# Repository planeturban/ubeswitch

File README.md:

## 301
Needed to keep it clean. BOM and other stuff is over here -> https://github.com/planeturban/ubeswitchmk6

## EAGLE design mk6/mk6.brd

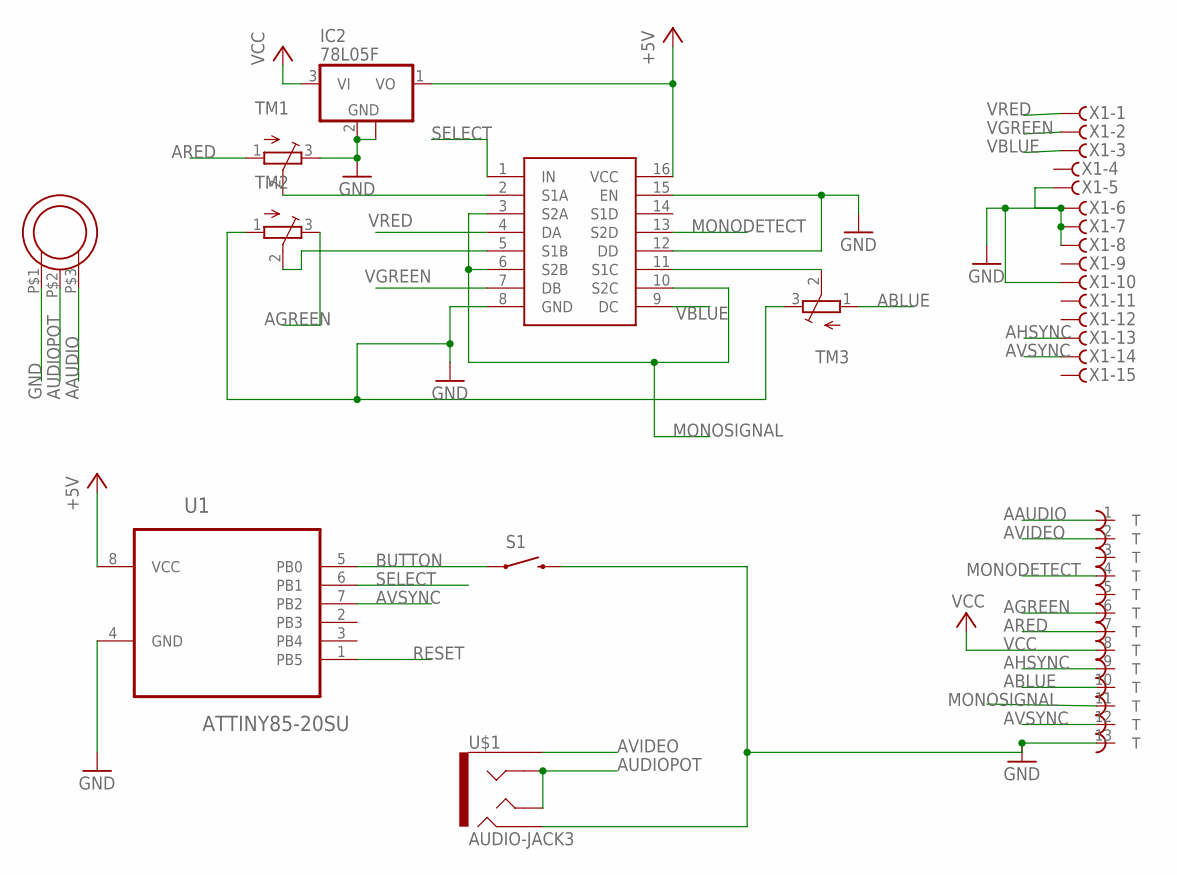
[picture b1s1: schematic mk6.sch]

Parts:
ATARIOUT: DIN13T; ADADS
IC2: 78L05F; SOT89
S1: SWITCH-MOMENTARY-2TACTILE-SWITCH-SMD-RIGHT-ANGLE; TACTILE_SWITCH-SMD-RIGHT-ANGLE
TM1, TM2, TM3: TRIMPOTTC33X; TC33X
TS5V330: V330; SOIC16N
U1: ATTINY85-20SU; SOIC127P798X216-8N
U$1: AUDIO-JACK3; AUDIO-JACK-TRRS-SMD
U$2: DB-1001N; THUMB_POT
X1: F15HDVS; HDF15V

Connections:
+5V: IC2.1 (VO), TS5V330.16 (VCC), U1.8 (VCC)
AAUDIO: ATARIOUT.1, U$2.P$3 (3)
ABLUE: ATARIOUT.10, TM3.1 (A)
AGREEN: ATARIOUT.6, TM2.3 (E)
AHSYNC: ATARIOUT.9, X1.13
ARED: ATARIOUT.7, TM1.1 (A)
AUDIOPOT: U$1.RING1, U$1.TIP, U$2.P$2 (2)
AVIDEO: ATARIOUT.2, U$1.EARTH
AVSYNC: ATARIOUT.12, U1.7 (PB2), X1.14
BUTTON: S1.1, U1.5 (PB0)
GND: ATARIOUT.13, IC2.2 (GND), IC2.2@1 (GND), S1.2, TM1.3 (E), TM2.1 (A), TM3.3 (E), TS5V330.8 (GND), TS5V330.12 (DD), TS5V330.15 (EN), U1.4 (GND), U$1.RING2, U$2.P$1 (1), X1.5, X1.6, X1.7, X1.8, X1.10
MONODETECT: ATARIOUT.4, TS5V330.13 (S2D)
MONOSIGNAL: ATARIOUT.11, TS5V330.3 (S2A), TS5V330.6 (S2B), TS5V330.10 (S2C)
unnamed: TM1.2 (S), TS5V330.2 (S1A)
unnamed: TM2.2 (S), TS5V330.5 (S1B)
unnamed: TM3.2 (S), TS5V330.11 (S1C)
RESET: U1.1 (PB5)
SELECT: TS5V330.1 (IN), U1.6 (PB1)
VBLUE: TS5V330.9 (DC), X1.3
VCC: ATARIOUT.8, IC2.3 (VI)
VGREEN: TS5V330.7 (DB), X1.2
VRED: TS5V330.4 (DA), X1.1

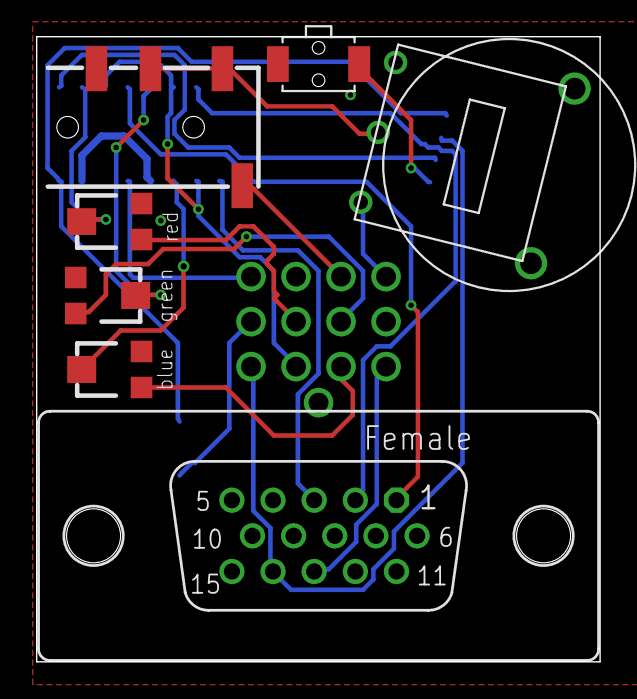
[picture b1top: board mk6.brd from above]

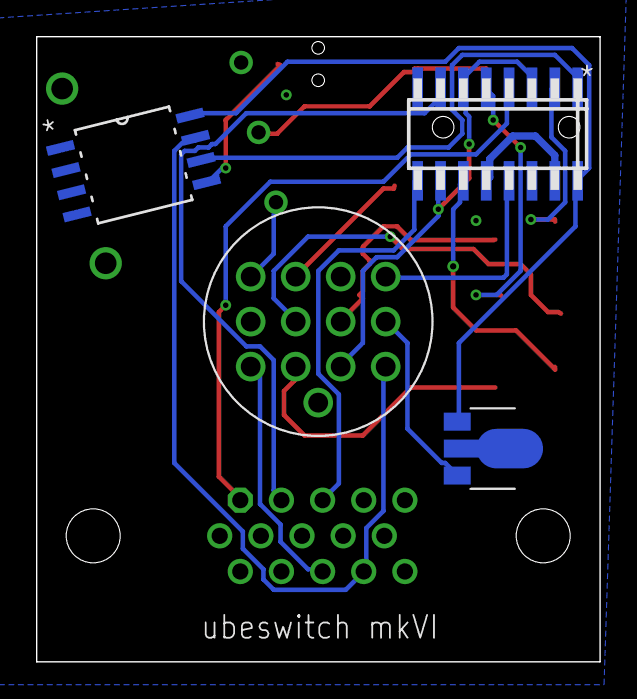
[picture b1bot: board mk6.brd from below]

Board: 2 copper layers, 31.3 x 34.7 mm, 11 parts (4 on the bottom side), 21 nets.

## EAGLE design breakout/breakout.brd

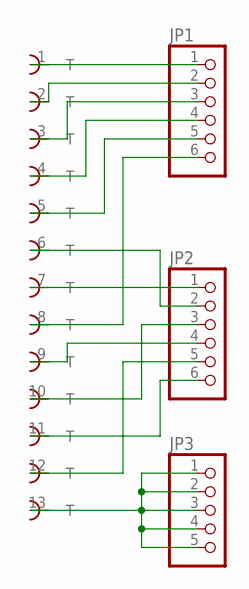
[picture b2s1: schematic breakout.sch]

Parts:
J1: DIN13T; ADADS
JP1, JP2: PINHD-1X6; 1X06
JP3: PINHD-1X5; 1X05

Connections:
GND: J1.13, JP3.1, JP3.2, JP3.3, JP3.4, JP3.5
unnamed: J1.1, JP1.1
unnamed: J1.2, JP1.2
unnamed: J1.3, JP1.3
unnamed: J1.4, JP1.4
unnamed: J1.5, JP1.5
unnamed: J1.7, JP2.1
unnamed: J1.6, JP2.2
unnamed: J1.8, JP1.6
unnamed: J1.10, JP2.3
unnamed: J1.11, JP2.6
unnamed: J1.9, JP2.4
unnamed: J1.12, JP2.5

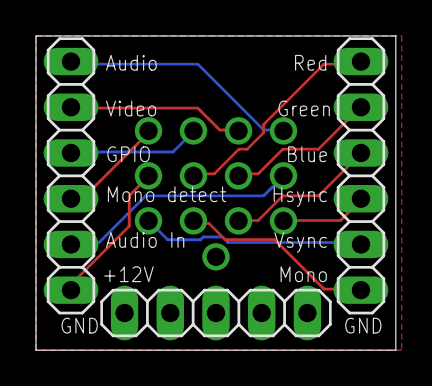
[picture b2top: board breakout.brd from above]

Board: 2 copper layers, 20.0 x 17.5 mm, 4 parts (1 on the bottom side), 13 nets.

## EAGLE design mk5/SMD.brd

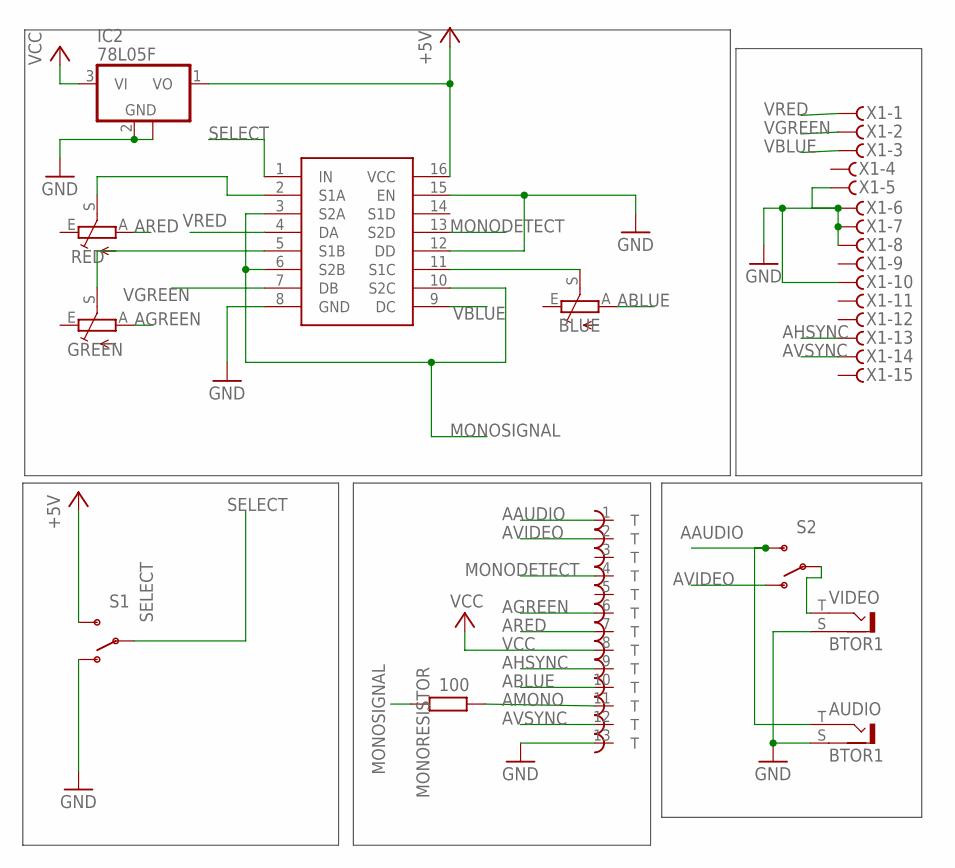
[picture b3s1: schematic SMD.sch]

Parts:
ATARIOUT: DIN13T; ADADS
AUDIO: BTOR1
BLUE: TRIM_EU-CA6H; CA6H
GREEN: TRIM_EU-CA6H; CA6H
IC2: 78L05F; SOT89
MONORESISTOR: 100; R1206
RED: TRIM_EU-CA6H; CA6H
S1, S2: SWITCH-SPDT-SMD-A; SWITCH-SPST-SMD-A
TS5V330: V330; SOIC16N
VIDEO: BTOR1
X1: F15HDVS; HDF15V

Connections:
+5V: IC2.1 (VO), S1.3 (S), TS5V330.16 (VCC)
A/V-PIN: S2.2, VIDEO.T (1)
AAUDIO: ATARIOUT.1, AUDIO.T (1), S2.3 (S)
ABLUE: ATARIOUT.10, BLUE.A
AGREEN: ATARIOUT.6, GREEN.A
AHSYNC: ATARIOUT.9, X1.13
AMONO: ATARIOUT.11, MONORESISTOR.2
ARED: ATARIOUT.7, RED.A
AVIDEO: ATARIOUT.2, S2.1 (O)
AVSYNC: ATARIOUT.12, X1.14
BOUT: BLUE.S, TS5V330.11 (S1C)
GND: ATARIOUT.13, AUDIO.S (2), IC2.2 (GND), IC2.2@1 (GND), S1.1 (O), TS5V330.8 (GND), TS5V330.12 (DD), TS5V330.15 (EN), VIDEO.S (2), X1.5, X1.6, X1.7, X1.8, X1.10
GOUT: GREEN.S, TS5V330.5 (S1B)
MONODETECT: ATARIOUT.4, TS5V330.13 (S2D)
MONOSIGNAL: MONORESISTOR.1, TS5V330.3 (S2A), TS5V330.6 (S2B), TS5V330.10 (S2C)
ROUT: RED.S, TS5V330.2 (S1A)
SELECT: S1.2, TS5V330.1 (IN)
VBLUE: TS5V330.9 (DC), X1.3
VCC: ATARIOUT.8, IC2.3 (VI)
VGREEN: TS5V330.7 (DB), X1.2
VRED: TS5V330.4 (DA), X1.1

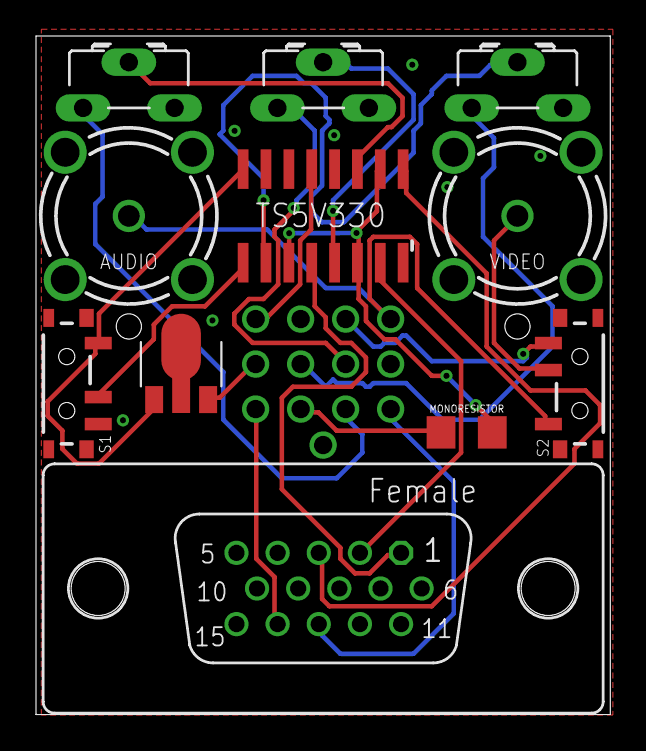
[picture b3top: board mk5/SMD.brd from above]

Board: 2 copper layers, 31.9 x 37.7 mm, 12 parts (1 on the bottom side), 21 nets.

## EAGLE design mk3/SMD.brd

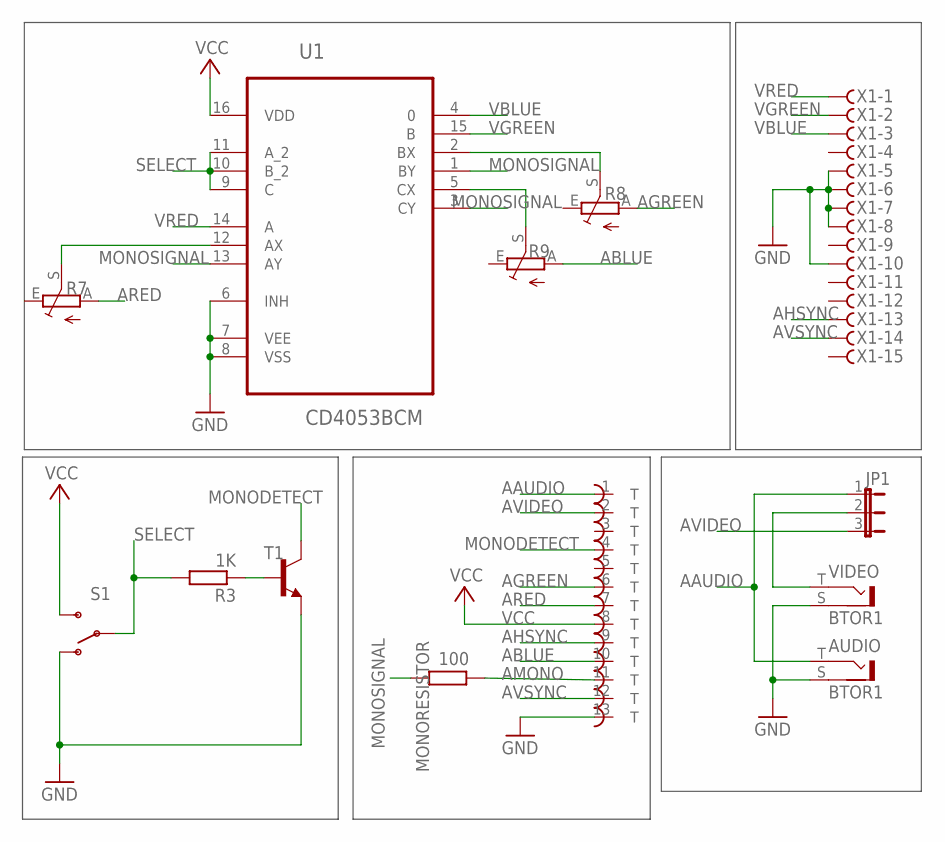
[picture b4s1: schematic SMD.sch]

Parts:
ATARIOUT: DIN13T; ADADS
AUDIO: BTOR1
JP1: JP2E; JP2
MONORESISTOR: 100; 0207/2V
R3: 1K; M1206
R7, R8, R9: TRIM_EU-CA6H; CA6H
S1: SWITCH-SPDT-SMD-A; SWITCH-SPST-SMD-A
T1: MMBT3904LT1-NPN-SOT23-BEC; SOT23-BEC
U1: CD4053BCM; SOIC127P600X175-16N
VIDEO: BTOR1
X1: F15HDVS; HDF15V

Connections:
AAUDIO: ATARIOUT.1, AUDIO.T (1), JP1.1
ABLUE: ATARIOUT.10, R9.A
AGREEN: ATARIOUT.6, R8.A
AHSYNC: ATARIOUT.9, X1.13
AMONO: ATARIOUT.11, MONORESISTOR.2
ARED: ATARIOUT.7, R7.A
AVIDEO: ATARIOUT.2, JP1.3
AVSYNC: ATARIOUT.12, X1.14
GND: ATARIOUT.13, AUDIO.S (2), S1.1 (O), T1.E, U1.6 (INH), U1.7 (VEE), U1.8 (VSS), VIDEO.S (2), X1.5, X1.6, X1.7, X1.8, X1.10
MONODETECT: ATARIOUT.4, T1.C
MONOSIGNAL: MONORESISTOR.1, U1.1 (BY), U1.3 (CY), U1.13 (AY)
unnamed: R7.S, U1.12 (AX)
unnamed: JP1.2, VIDEO.T (1)
unnamed: R8.S, U1.2 (BX)
unnamed: R9.S, U1.5 (CX)
unnamed: R3.1, T1.B
SELECT: R3.2, S1.2, U1.9 (C), U1.10 (B_2), U1.11 (A_2)
VBLUE: U1.4 (0), X1.3
VCC: ATARIOUT.8, S1.3 (S), U1.16 (VDD)
VGREEN: U1.15 (B), X1.2
VRED: U1.14 (A), X1.1

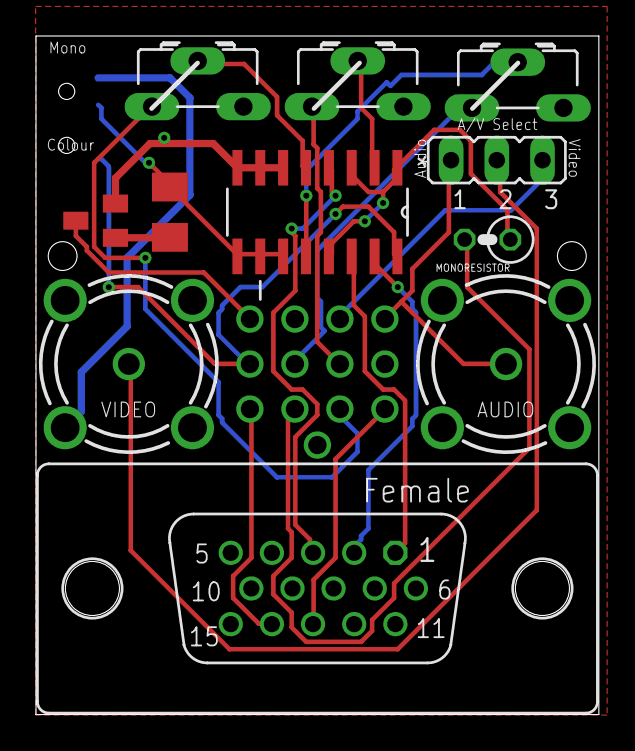
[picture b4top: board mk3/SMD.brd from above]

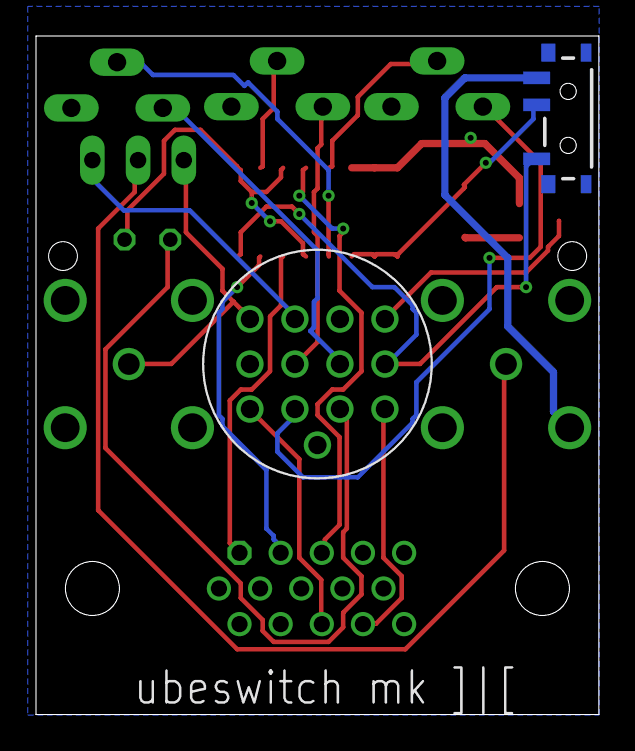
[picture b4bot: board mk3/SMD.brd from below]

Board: 2 copper layers, 31.3 x 37.7 mm, 13 parts (2 on the bottom side), 21 nets.

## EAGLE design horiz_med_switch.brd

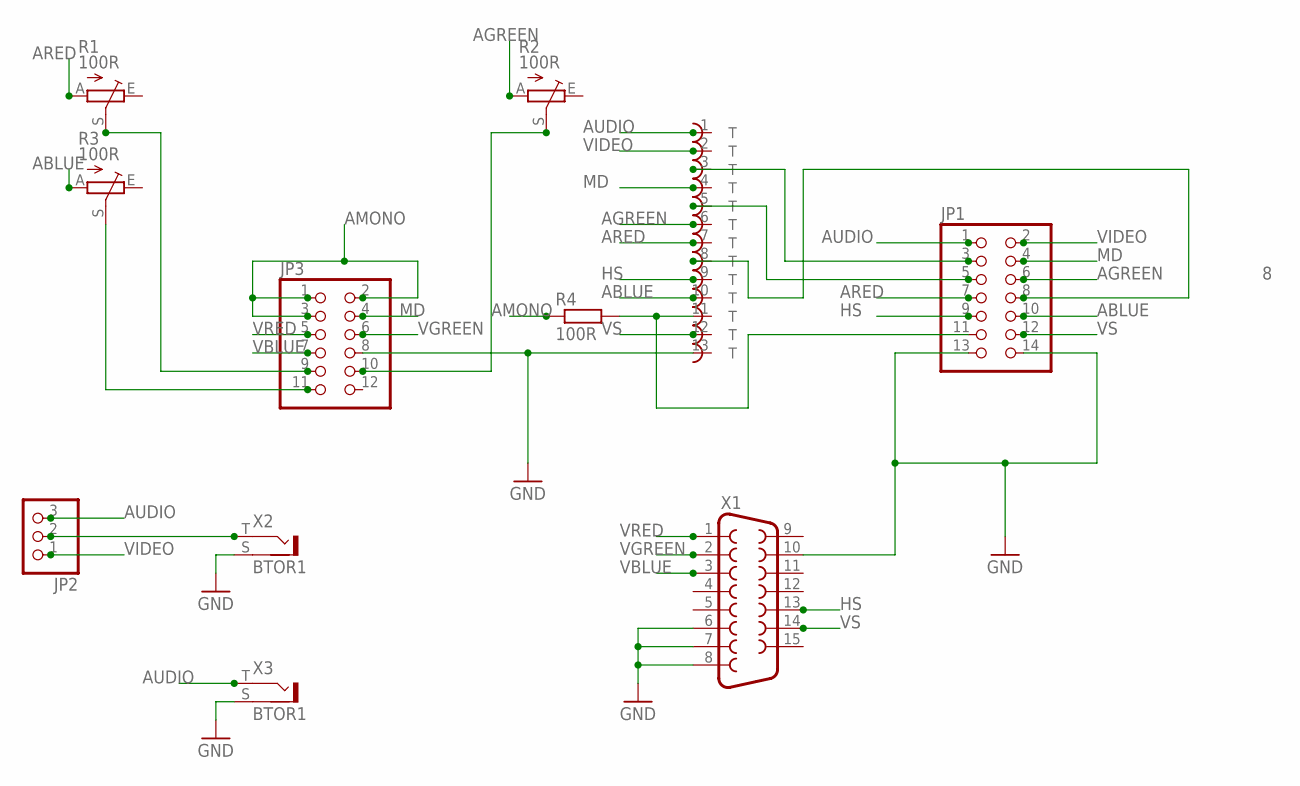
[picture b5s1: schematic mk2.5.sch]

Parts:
J1: DIN13T; ADADS
JP1: PINHD-2X7; 2X07
JP2: PINHD-1X3; 1X03
JP3: PINHD-2X6; 2X06
R1, R2, R3: 100R; CA6H
R4: 100R; 0204/5
X1: F15HDV; HDF15V
X2, X3: BTOR1

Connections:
8: J1.8, JP1.8
ABLUE: J1.10, JP1.10, R3.A
AGREEN: J1.6, JP1.6, R2.A
AMONO: JP3.1, JP3.2, JP3.3, R4.1
ARED: J1.7, JP1.7, R1.A
AUDIO: J1.1, JP1.1, JP2.3, X3.T (1)
GND: J1.13, JP1.13, JP1.14, JP3.8, X1.6, X1.7, X1.8, X1.10, X2.S (2), X3.S (2)
HS: J1.9, JP1.9, X1.13
MD: J1.4, JP1.4, JP3.4
unnamed: J1.11, JP1.11, R4.2
unnamed: JP3.9, R1.S
unnamed: JP3.10, R2.S
unnamed: JP2.2, X2.T (1)
unnamed: JP3.11, R3.S
unnamed: J1.3, JP1.3
unnamed: J1.5, JP1.5
VBLUE: JP3.7, X1.3
VGREEN: JP3.6, X1.2
VIDEO: J1.2, JP1.2, JP2.1
VRED: JP3.5, X1.1
VS: J1.12, JP1.12, X1.14

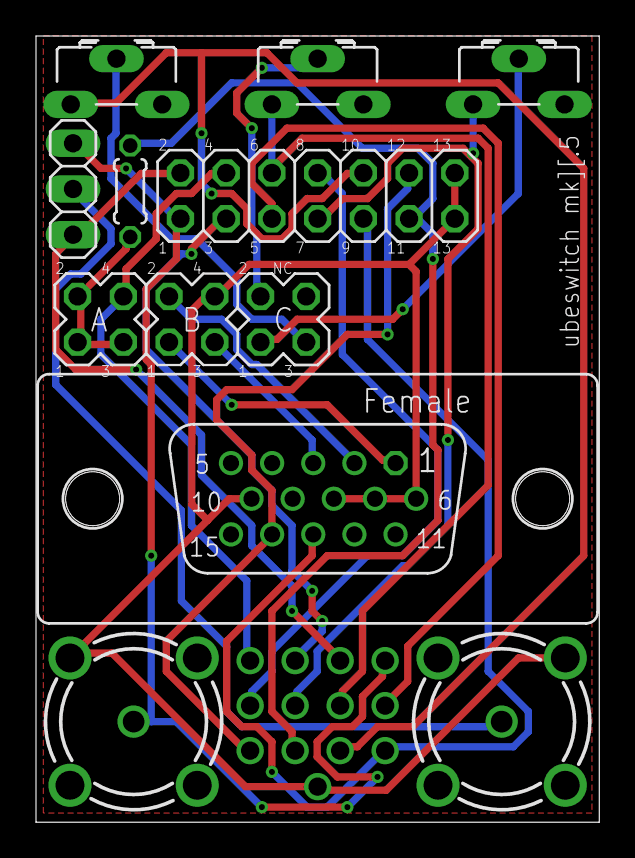
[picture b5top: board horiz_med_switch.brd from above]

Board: 2 copper layers, 31.3 x 43.7 mm, 11 parts (1 on the bottom side), 21 nets.

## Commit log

2016-09-30 First.
2016-09-30 add gitignore to .gitignore
2016-09-30 Added license
2016-09-30 .gitignore.
2016-10-07 Rename.
2016-10-10 Added mk3, images, moved mk2.5
2016-10-10 readme
2016-10-10 .gitignore
2016-10-10 Changed base resistor to 1k.
2016-10-10 Roberto
2016-10-11 Locked the connectors.
2016-10-12 Switched to CD4053, didn't check the ratings on the HC-one.
2016-10-13 Cleanup
2016-10-13 CD4053
2017-03-07 mk5. Whatever happened to mk4? Nobody knows.
2017-03-07 No THT for you!
2017-03-07 Removed obsolete mk3.
2017-03-07 Update image.
2017-03-07 Added partlist.txt
2017-03-07 Added notes in partlist
2017-03-07 Forgot how to English. More info, about trim pots.
2017-03-15 Swapped switch pins on A/V switch, to make it easier to patch video to video RCA.
2017-04-13 Better placement of vias, to minimize risk of bridging.
2017-04-20 Update to reflect reality.
    Plus fixed typo. Hate 'em.
2017-04-20 Breadout board.
2017-04-22 Breakout, logical placement of the headers
2017-04-30 Why not group things together?
2017-06-30 Version 5.1 Removed RCAs
2017-06-30 BEtter placement of TS5V330
2017-08-10 code and stuff
2017-08-10 Replaced RCAs for 3.5mm
2017-08-13 Are we there yet?
2017-08-15 Shorter switch time
2017-08-16 'Trying to do things properly often comes back to haunt you' - Exxos. Moved a via that could mess things up. Modified the footprint of the button to make it easier when soldering.
2018-01-08 Update LICENSE
2018-03-25 Update README.md
    moved

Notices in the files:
parts and their libraries:
SparkFun-Electromechanical: Licensing: Creative Commons ShareAlike 4.0 International - https://creativecommons.org/licenses/by-sa/4.0
